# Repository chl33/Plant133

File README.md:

# Plant133

This is a full distribution of the Plant133 plant-watering device. This device can monitor and water up to 4 plants at a time. This repository hosts the firmware, PCBA design, and OpenSCAD code for all components.

A writeup about this project is at "[Plant1337: "Water 4 plants](https://selectiveappeal.org/posts/plant1337/)."

## Features

*   **Multi-Plant Support**: Monitors and independently waters up to 4 plants.
*   **Sensors**:
    *   Capacitive soil moisture sensing for each plant.
    *   SHTC3 temperature and humidity sensor for environmental monitoring.
    *   Reservoir water level float switch detection.
*   **User Interface**:
    *   **OLED Screen**: Rotates through status screens showing IP address, moisture levels, and environment data.
    *   **Web Dashboard**: A modern Svelte-based responsive web interface for real-time monitoring and configuration.
*   **Integration**:
    *   **MQTT**: Full support for Home Assistant auto-discovery and state reporting.
*   **Safety**:
    *   **Watchdog Timer**: Hardware watchdog protects against system hangs.
    *   **Dose Limiting**: Prevents over-watering by limiting the maximum number of pump cycles per day.
    *   **Reservoir Check**: Prevents pump damage by detecting low water levels.

## Usage

Please see the [instructions](instructions.md) for how to assemble and set up a Plant133 device hardware.

## Development

### Prerequisites
*   [PlatformIO](https://platformio.org/) (Core or VSCode extension)
*   [Node.js](https://nodejs.org/) (for building the web interface)

### Building and Flashing Firmware

1.  **Configure Secrets**: Copy `secrets.ini.example` to `secrets.ini` and set your WiFi credentials, OTA password, and MQTT details.
2.  **Onetime setup for building the web interface**:
    ```bash
	cd svelte
	npm install
	```
3.  **Build the Web interface and Firmware**:
    ```bash
    # For a specific board (e.g. usb_cactus)
    pio run -e usb_cactus
    ```
4.  **Upload Firmware**:
    ```bash
    pio run -e usb_cactus -t upload
    ```

## API Reference

The device exposes a JSON API for integration and control:

*   `GET /api/status`: Returns system status (temp, humidity, water level, MQTT connection).
*   `GET /api/plants`: Returns configuration for all plants.
*   `GET /api/moisture`: Returns current moisture readings and watering states.
*   `PUT /api/plants/{id}`: Update configuration for a specific plant.
*   `GET /api/wifi`: Get current WiFi SSID and board name.
*   `GET /api/mqtt`: Get MQTT configuration status.
*   `POST /test/pump`: Run a pump for a specific duration (JSON body: `{ "pumpId": 1, "duration": 1000 }`).
*   `POST /api/restart`: Restart the device.

## Software Libraries

This project is built using a custom C++ framework for ESP devices:
- [og3](https://github.com/chl33/og3): Application framework.
- [og3x-oled](https://github.com/chl33/og3x-oled): OLED screen support.
- [og3x-shtc3](https://github.com/chl33/og3x-shtc3): SHTC3 sensor support.
- [svelteesp32](https://github.com/BCsabaEngine/svelteesp32): Web interface integration.

## Hardware

### PCBA

The full [KiCAD](https://www.kicad.org/) project for the printed circuit board is in the [KiCAD](KiCAD/) subdirectory.

### 3D Printed Components

Components are designed in [OpenSCAD](https://openscad.org/). Source code is in the [scad](scad/) subdirectory.

#### Project box
Housing for the PCBA ([scad/box/](scad/box/)).

#### Reservoir Hanger
Mounts the box to a water reservoir ([scad/ebox_hook](scad/ebox_hook)).

#### Reservoir Insert
Holds pumps and water level float ([scad/reservoir_insert](scad/reservoir_insert)).

#### Moisture Sensor Cap
Holds the watering tube at the sensor location ([scad/moisture_sensor_cap](scad/moisture_sensor_cap)).

#### Watering Spike
Alternative watering method using a soil spike ([scad/spike](scad/spike)).

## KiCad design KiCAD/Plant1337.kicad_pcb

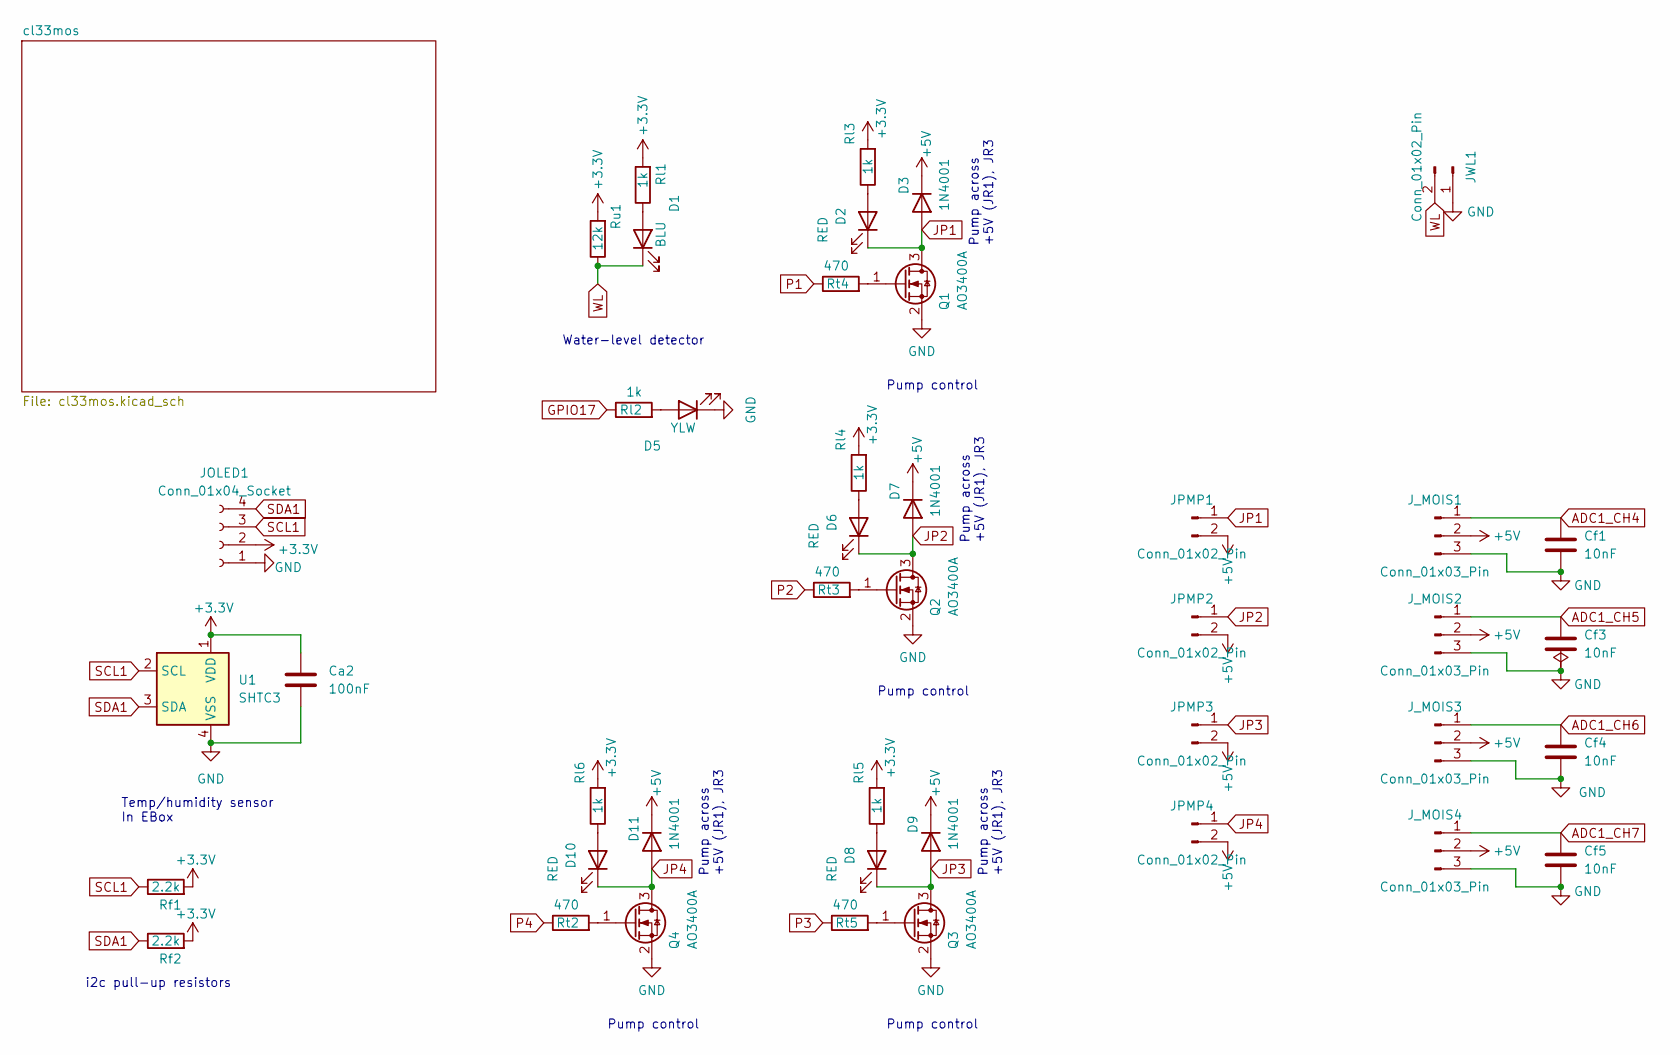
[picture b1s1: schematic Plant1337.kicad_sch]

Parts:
Ca2: 100nF; C_0603_1608Metric
Cf1, Cf3, Cf4, Cf5: 10nF; C_0603_1608Metric_Pad1.08x0.95mm_HandSolder
D1: BLU; LED_0603_1608Metric
D2, D6, D8, D10: RED; LED_0603_1608Metric
D3, D7, D9, D11: 1N4001; D_SMA
D5: YLW; LED_0603_1608Metric
JOLED1: Conn_01x04_Socket; PinSocket_1x04_P2.54mm_Vertical
JPMP1, JPMP2, JPMP3, JPMP4: Conn_01x02_Pin; JST_XH_B2B-XH-A_1x02_P2.50mm_Vertical
JWL1: Conn_01x02_Pin; JST_XH_B2B-XH-A_1x02_P2.50mm_Vertical
J_MOIS1, J_MOIS2, J_MOIS3, J_MOIS4: Conn_01x03_Pin; JST_XH_B3B-XH-A_1x03_P2.50mm_Vertical
Q1, Q2, Q3, Q4: AO3400A; SOT-23
Rf1, Rf2: 2.2k; R_0603_1608Metric
Rl1, Rl2, Rl3, Rl4, Rl5, Rl6: 1k; R_0603_1608Metric
Rt2, Rt3, Rt4, Rt5: 470; R_0603_1608Metric
Ru1: 12k; R_0603_1608Metric
U1: SHTC3; Sensirion_DFN-4-1EP_2x2mm_P1mm_EP0.7x1.6mm

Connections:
+3.3V: Ca2.1, JOLED1.2, Rf1.2, Rf2.2, Rl1.2, Rl3.2, Rl4.2, Rl5.2, Rl6.2, Ru1.2, U1.1 (VDD); also elsewhere on the board
+5V: D3.1 (K), D7.1 (K), D9.1 (K), D11.1 (K), JPMP1.2, JPMP2.2, JPMP3.2, JPMP4.2, J_MOIS1.2, J_MOIS2.2, J_MOIS3.2, J_MOIS4.2; also elsewhere on the board
ADC1_CH4: Cf1.2, J_MOIS1.1; also elsewhere on the board
ADC1_CH5: Cf3.2, J_MOIS2.1; also elsewhere on the board
ADC1_CH6: Cf4.2, J_MOIS3.1; also elsewhere on the board
ADC1_CH7: Cf5.2, J_MOIS4.1; also elsewhere on the board
GND: Ca2.2, Cf1.1, Cf3.1, Cf4.1, Cf5.1, D5.1 (K), JOLED1.1, JWL1.1, J_MOIS1.3, J_MOIS2.3, J_MOIS3.3, J_MOIS4.3, Q1.2 (S), Q2.2 (S), Q3.2 (S), Q4.2 (S), U1.4 (VSS); also elsewhere on the board
GPIO17: Rl2.1; also elsewhere on the board
JP1: D2.1 (K), D3.2 (A), JPMP1.1, Q1.3 (D)
JP2: D6.1 (K), D7.2 (A), JPMP2.1, Q2.3 (D)
JP3: D8.1 (K), D9.2 (A), JPMP3.1, Q3.3 (D)
JP4: D10.1 (K), D11.2 (A), JPMP4.1, Q4.3 (D)
unnamed: D1.2 (A), Rl1.1
unnamed: D2.2 (A), Rl3.1
unnamed: D5.2 (A), Rl2.2
unnamed: D6.2 (A), Rl4.1
unnamed: D8.2 (A), Rl5.1
unnamed: D10.2 (A), Rl6.1
unnamed: Q1.1 (G), Rt4.2
unnamed: Q2.1 (G), Rt3.2
unnamed: Q3.1 (G), Rt5.2
unnamed: Q4.1 (G), Rt2.2
P1: Rt4.1; also elsewhere on the board
P2: Rt3.1; also elsewhere on the board
P3: Rt5.1; also elsewhere on the board
P4: Rt2.1; also elsewhere on the board
SCL1: JOLED1.3, Rf1.1, U1.2 (SCL); also elsewhere on the board
SDA1: JOLED1.4, Rf2.1, U1.3 (SDA); also elsewhere on the board
WL: D1.1 (K), JWL1.2, Ru1.1; also elsewhere on the board

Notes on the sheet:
i2c pull-up resistors
Pump control
Pump across +5V (JR1), JR3
Water-level detector
Temp/humidity sensor In EBox

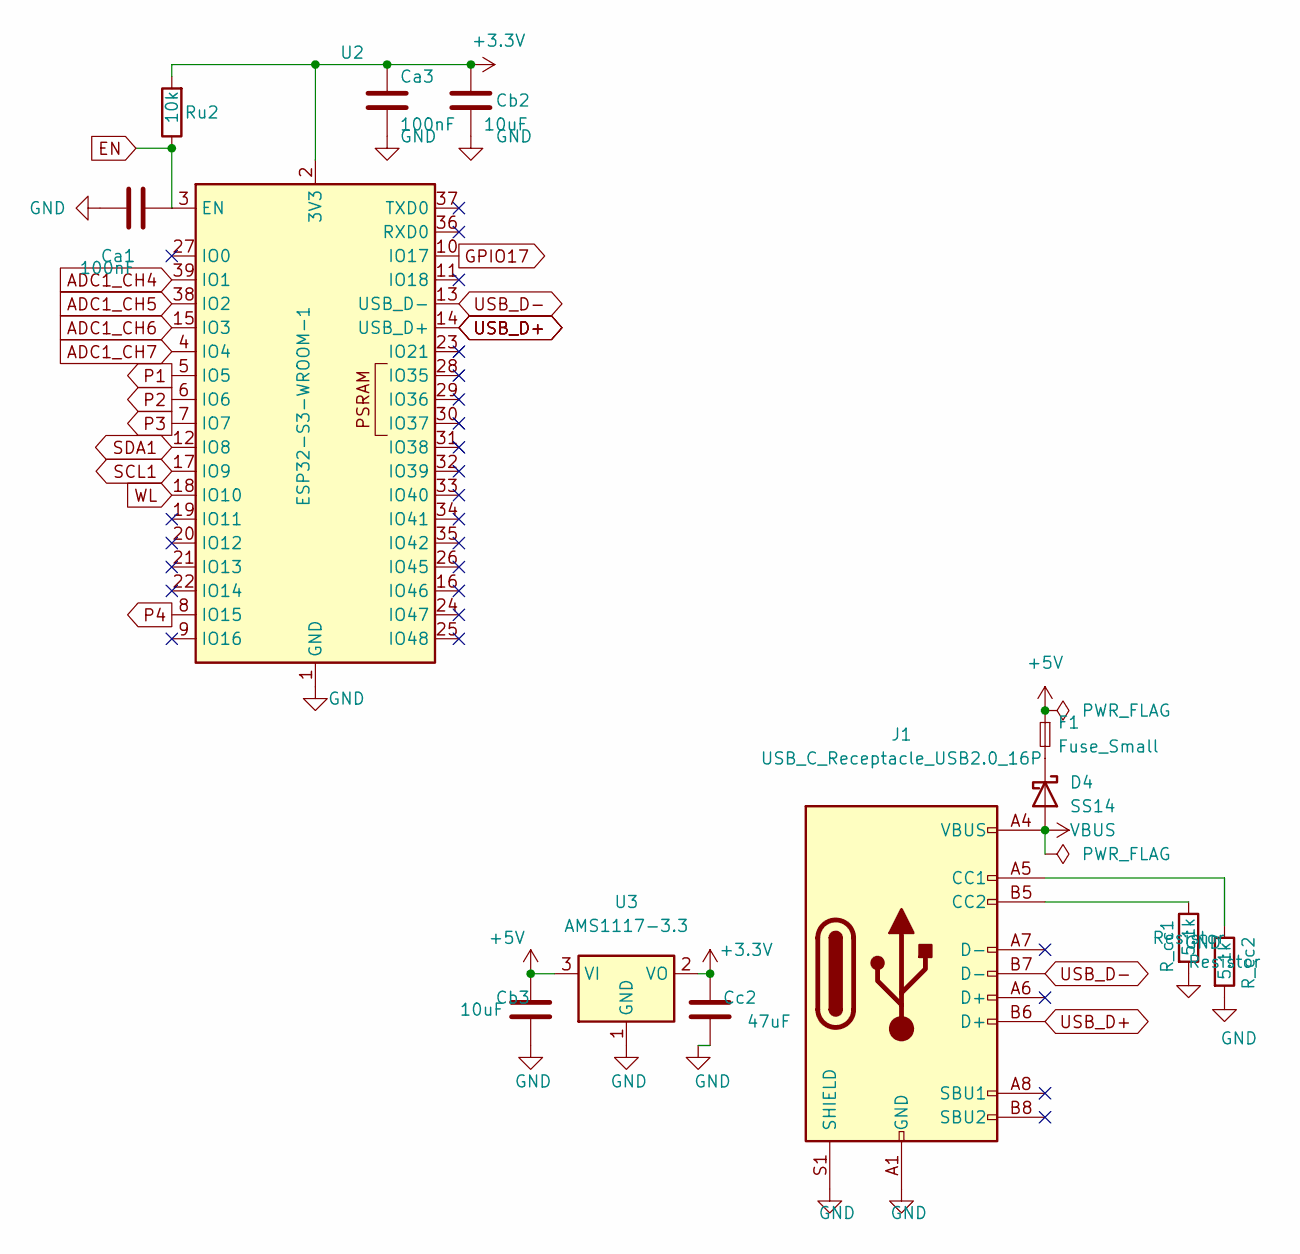
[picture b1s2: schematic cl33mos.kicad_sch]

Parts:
Ca1, Ca3: 100nF; C_0603_1608Metric
Cb2, Cb3: 10uF; C_0805_2012Metric_Pad1.18x1.45mm_HandSolder
Cc2: 47uF; C_0805_2012Metric_Pad1.18x1.45mm_HandSolder
D4: SS14; D_SMA
F1: Fuse_Small; D_0805_2012Metric
J1: USB_C_Receptacle_USB2.0_16P; USB_C_Receptacle_HRO_TYPE-C-31-M-12
R_cc1, R_cc2: 5.1k; R_0603_1608Metric
Ru2: 10k; R_0603_1608Metric
U2: ESP32-S3-WROOM-1
U3: AMS1117-3.3; SOT-223-3_TabPin2

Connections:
+3.3V: Ca3.1, Cb2.1, Cc2.1, Ru2.2, U2.2 (3V3), U3.2 (VO); also elsewhere on the board
+5V: Cb3.1, F1.1, U3.3 (VI); also elsewhere on the board
ADC1_CH4: U2.39 (IO1); also elsewhere on the board
ADC1_CH5: U2.38 (IO2); also elsewhere on the board
ADC1_CH6: U2.15 (IO3); also elsewhere on the board
ADC1_CH7: U2.4 (IO4); also elsewhere on the board
EN: Ca1.2, Ru2.1, U2.3 (EN)
GND: Ca1.1, Ca3.2, Cb2.2, Cb3.2, Cc2.2, J1.A1 (GND), J1.A12 (GND), J1.B1 (GND), J1.B12 (GND), J1.S1 (SHIELD), R_cc1.2, R_cc2.2, U2.1 (GND), U2.40 (GND), U2.41 (GND), U3.1 (GND); also elsewhere on the board
GPIO17: U2.10 (IO17); also elsewhere on the board
unnamed: D4.1 (K), F1.2
unnamed: J1.A5 (CC1), R_cc2.1
unnamed: J1.B5 (CC2), R_cc1.1
P1: U2.5 (IO5); also elsewhere on the board
P2: U2.6 (IO6); also elsewhere on the board
P3: U2.7 (IO7); also elsewhere on the board
P4: U2.8 (IO15); also elsewhere on the board
SCL1: U2.17 (IO9); also elsewhere on the board
SDA1: U2.12 (IO8); also elsewhere on the board
USB_D+: J1.B6 (D+), U2.14 (USB_D+)
USB_D-: J1.B7 (D-), U2.13 (USB_D-)
VBUS: D4.2 (A), J1.A4 (VBUS), J1.A9 (VBUS), J1.B4 (VBUS), J1.B9 (VBUS)
WL: U2.18 (IO10); also elsewhere on the board

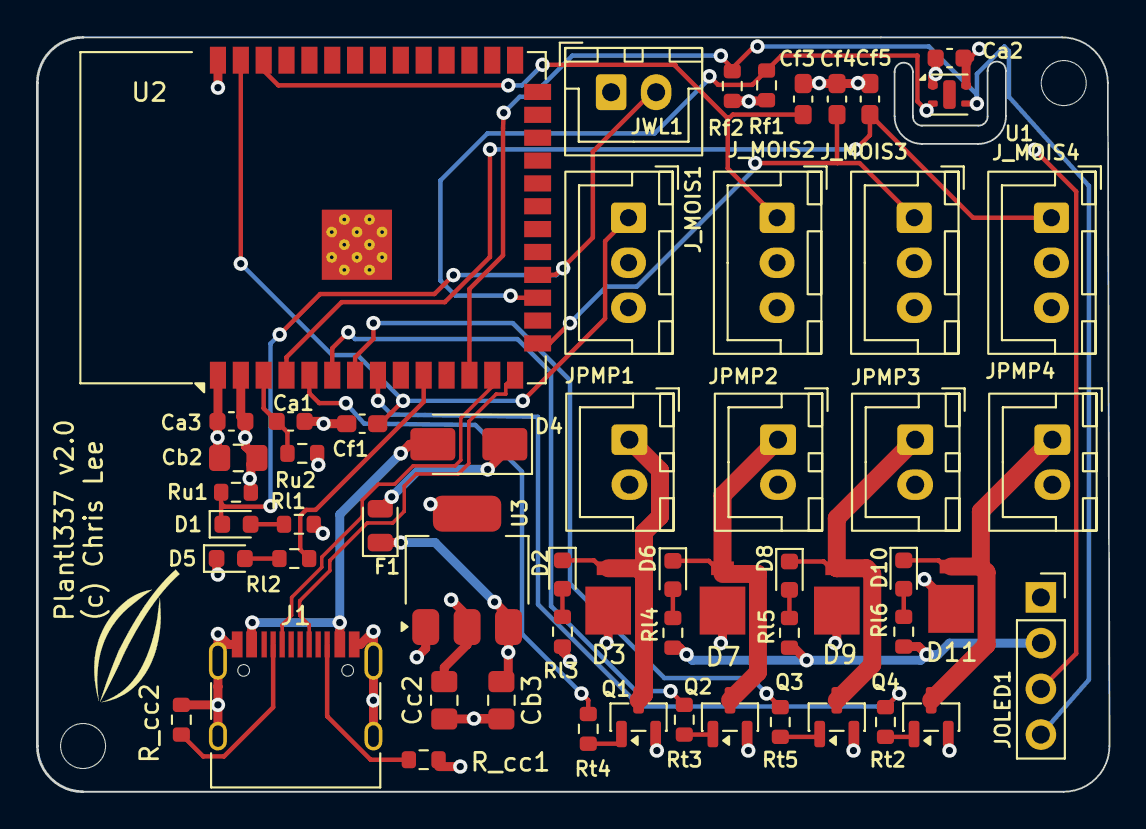
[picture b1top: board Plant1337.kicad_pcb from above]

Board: 4 copper layers, 59.6 x 41.9 mm, 56 parts (0 on the bottom side), 36 nets.

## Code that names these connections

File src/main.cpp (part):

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constexpr uint8_t kWaterPin = 23;
constexpr uint8_t kModeLED = 17;
// Soil moisture sensor ADC pin assignments for classic ESP32 (ADC1: GPIO 32, 33, 34, 35)
// - gpio32: adc1_ch4 -> mois1
// - gpio33: adc1_ch5 -> mois2
// - gpio34: adc1_ch6 -> mois3
// - gpio35: adc1_ch7 -> mois4
constexpr uint8_t kMoistureAnalogPin[4] = {32, 33, 34, 35};
// The pins on the v1.3 board. Changed pump-2 pin to not be on when power is first applied.
constexpr uint8_t kPumpCtlPin[4] = {18, 13, 16, 19};
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
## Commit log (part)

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2024-07-20 initial version
2024-07-20 Organize web pages by plant
2024-07-21 Add project box and utilities
2024-07-21 add readme
2024-07-21 add copyright check
2024-07-21 copyrights
2024-07-21 add pre-commit format check
2024-07-21 Initial content (#1)
    * initial version
    * Organize web pages by plant
    * Add project box and utilities
    * add readme
    * add copyright check
    * copyrights
2024-08-04 box: add screw-holes for box bottom, to attach to reservoir-hook
2024-08-04 fix watering state names
2024-08-04 Initial deployable software version
    - ADC/moisture pins for latest PCB version
    - OLED: graphical display of moisture states
    - Configuration page for reservoir pump-secs after float goes low
    - Offset timing of state machines for different plants
2024-08-04 added license
2024-08-04 copyright check: check .scad files
2024-08-04 Deployment 1 (#2)
    - box: add screw-holes for box bottom, to attach to reservoir-hook
    - fix watering state names
    - ADC/moisture pins for latest PCB version
    - OLED: graphical display of moisture states
    - Configuration page for reservoir pump-secs after float goes low
    - Offset timing of state machines for different plants
2024-08-04 add hump for OLED screen
2024-08-04 box: gui.py: button for launching OpenSCAD
2024-08-04 box update (#3)
    * add hump for OLED screen
    * box: gui.py: button for launching OpenSCAD
2024-08-09 update for og3 version0.2.0 (#4)
2024-08-10 finished porting to 0.2.0
2024-08-10 finished porting to 0.2.0 (#5)
2024-08-31 Move ebox to scad/box, and add number-labels for connectors.
2024-09-19 Update drawing of moisture level on OLED
    For each plant, scale so screen Y-range maps to twice min/max
    %-moisture targets and is centered between these.
2024-09-19 Add model of soil watering-spike.
2024-09-19 add platform-io compile check to workflow
2024-09-19 Openscad & code updates (#6)
    - Move EBox to a `scad/box` subdirectory, and add number-labels for plant connectors.
    - Improve drawing of moisture level on OLED screen
    - Add OpenSCAD model of a soil-spike with holes for watering.
    - Added compile-check
2024-09-19 LED blinking only for plant0
2024-09-21 improve comments in main.cpp
2024-09-21 KiCAD project for the Plant1337 PCB
2024-09-21 add reservoir insert OpenSCAD code
2024-09-21 fix Ebox
2024-09-21 OpenSCAD source for moisture sensor cap.
2024-09-21 update readme, add images
2024-09-21 readme fixes
2024-09-21 Comments, OpenSCAD sources, README updates (#8)
    * Improved comments in main.cpp
    * Added KiCAD project for the Plant1337 PCB
    * OpenSCAD models additions and fixes
    * reservoir insert
    * moisture sensor cap.
    * fixed Ebox
2024-09-21 fix photo link
2024-09-21 shrink spike photo
2024-09-21 add ebox_hook to README
2024-09-21 add ebox (#9)
2024-10-01 Update: watering library.json, ebox hook, reservoir insert
    - EBox hook: make top thicker for robustness
    - Rservoir insert: 4-pump version
2024-10-01 first draft of instructions
2024-10-02 update gitignore
2024-10-02 rename, update instructions
2024-10-02 link instructions in readme
2024-10-02 Add first draft of instructions (#11)
2024-10-06 README: point at new blog post
2024-10-06 new picture
2024-10-06 README: point at new blog post (#12)
    * README: point at new blog post
    * new picture
2024-10-16 add images to instructions
2024-10-16 more images
2024-10-16 add images to instructions (#13)
2024-10-16 fix spike img
2024-10-16 fix spike img (#14)
2024-10-17 add more images to instructions (#15)
2024-10-19 Make seconds between pump does configurable.
2024-10-19 CI workflow: rename example .ini before testing
2024-10-19 Make seconds between pump does configurable. (#16)
    Also:
    - version -> 0.7.2
    - move example .ini files into place before platformio test build in CI
2024-10-19 Limit number of pump doses in a watering cycle
    If there are too many pump doses in watering cycle, then switch to a
    "watering paused" state and wait for 12 hours.
    This is a safety features to avoid over-watering if something goes wrong,
    such as unreliable moisture sensor readings.
2024-10-19 Limit number of pump doses in a watering cycle (#17)
    If there are too many pump doses in watering cycle, then switch to a
    "watering paused" state and wait for 12 hours.
    This is a safety features to avoid over-watering if something goes wrong,
    such as unreliable moisture sensor readings.
2024-10-19 Document new watering configuration options.
2024-10-19 update watering config image
2024-10-19 Document new watering configuration options. (#18)
    * Document new watering configuration options.
    * update watering config image
2024-10-19 Update og3 library, logging tweaks
2024-10-19 Update og3 library, logging tweaks (#19)
2024-10-19 og3x-oled version -> 0.2.2
2024-10-19 og3x-oled version -> 0.2.2 (#20)
2024-10-20 Set AP password (#21)
    - If specified in secrets.ini, set a password on the soft-AP.
    - Also, switch mqtt client library to that used by ESPHome.
2024-10-20 update instructions for AP mode improvements
2024-10-20 update instructions for AP mode improvements (#22)
2024-10-20 update deps: og3x-oled
2024-10-20 update deps: og3x-oled (#23)
2024-10-24 update workflows
2024-10-24 added license headers
2024-10-24 tweak workflow
2024-10-24 update workflows (#24)
    * update workflows
    * added license headers
2024-11-03 Limit watering doses per day, across multiple watering cycles.
2024-11-04 comments
2024-11-07 Limit watering doses per day, across multiple watering cycles. (#25)
2024-12-31 Port to og3 0.2.5
2024-12-31 Ensure pump is off when not in a state which is explicitly watering.
2024-12-31 Ensure pump is off when not in a state which is explicitly watering. (#27)
2025-01-11 Update KiCAD model
2025-01-12 Update KiCAD model (#28)
2025-01-20 Fix limiting doses in 24 hours.
    Use 64-bit clock values to avoid problems with value rollover.
2025-01-20 software version -> 0.8.0
2025-01-21 Simplify dose tracking, add some logging.
2025-01-23 Make end of watering-pause to be more consistent.
2025-01-23 dose tracking: minor tweak, update/fix comments
2025-01-24 Fix limiting doses in 24 hours. (#29)
    - Fix limiting doses in 24 hours.
    - Use 64-bit clock values to avoid problems with value rollover.
    - Make end of watering-pause to be more consistent.
    - software version -> 0.8.0
2025-06-28 Upgrade version of og3
    The new version of og3 does not support appending the variable-group name to variable
    names. In this version, we simply construct variable ids this way manually.
2025-07-22 Make a separate HA-discovery device for each plant
2025-07-30 DoseLog variables need per-plant differentiation
2025-08-01 HA discovery: set parent device for plants-devices
2025-08-01 version -> 0.8.3
2025-08-01 update copyright checker
2025-08-01 fix path
2025-08-01 fix license check again
2025-08-01 again
2025-08-01 ci fix?
2025-08-01 Version 0.8.3 (#30)
    * Make a separate HA-discovery device for each plant
    * Updated year in copyright notices
    * HA discovery: set parent device for plants-devices
    * version -> 0.8.3
    * update copyright checker
2025-08-10 KiCAD update -> v1.3. Change pump2 DIO, remove pump pull-downs
2025-10-05 board v1.3, test web page
2025-10-11 svelte app interface in progress
2025-10-12 Import svelte interface, add wifi API web backends
2025-10-12 MQTT svelte-config support added
2025-10-12 Layouty improvement from claude
2025-10-12 Add more config and status for each plant
2025-10-12 Failed (so far) attempt to display board top bar
2025-10-12 Claude: optimize for narrower (cellphone) screens
2025-10-13 Improvements
    - Fix setting plant "enabled" from svelte-interface
    - Fix saving mqtt/wifi config when updated from svelte-interface
    - Display improvements to interface
    - Include color bands for moisture gauge
    - Show raw moisture readings in config interface, for setting calibration values
2025-10-14 Compress gauge display on svelte overview page
2025-10-14 watering state machine: setState() updates m_watering_enabled.
2025-10-14 svelte interface: config via gear icon, update dose and status
2025-10-14 update version
2025-10-14 svelte interface: remove 0-100% at bottom of gauge
2025-10-15 svelte interface: MQTT connection indicator, sw/hw versions
2025-10-15 attempt to get CI to build svelte app
2025-10-18 attempt to fix CI build
2025-10-18 README: mention svelte web interface
2025-10-18 attempt to fix the CI build
2025-10-18 another attempt to fix the CI build
2025-10-18 update example secret.init files
2025-10-19 dependency update
2025-10-19 Use lib_compat_mode = strict to try to get code to compile
    Suggesed in https://community.platformio.org/t/im-having-trouble-with-library-dependencies-for-my-project/52855/2
2025-10-19 Add svelte-based web interface (#31)
    - Add svelte-based web UI developed with the help of claude.
    - KiCAD update -> v1.3. Change pump2 DIO, remove pump pull-downs
    - board v1.3, test web page
    The old interface can still be reached by at the "/root" path.
2025-10-19 Update README with svelte-interface picture
2025-10-19 README: mention the use of svelteesp32.
2025-10-23 KiCad updates, OpenSCAD design for PCB-stencil holder
2025-11-02 Added-back screw-holes at 2 corners of the board
2025-11-02 og3 -> 0.3.96
2025-11-28 gemini added: pump test button, app restart button
2025-11-28 Update software version, delete TODOs
2025-11-28 Multiple improvements (#33)
    - Version -> 0.9.2
    - Updated version of KiCAD
    - OpenSCAD design for PCB/stencil holder
    - Added screw holes in corners of PCB
    - Updated Web interface (gemini)
    - Restart button
2025-11-28 Use a watchdog timer for safety when pumping water (gemini)
2025-11-28 Use a watchdog timer for safety when pumping water (gemini) (#34)
2025-11-29 Disable watchdog timer during OTA firmware update
2025-11-29 Disable watchdog timer during OTA firmware update (#35)
2025-11-29 version bump: og3 version update
2025-11-29 Bump og3 again, revised README (gemini)
2025-11-29 tweaked readme
2025-11-29 Updated instructions (gemini)
2025-11-29 Updated instructions
2025-11-29 add missing images
2025-11-29 final instructions tweaks
2025-11-29 version bump: og3 version update (#36)
    * version bump: og3 version update
    * Revised README (gemini)
    * Updated instructions (gemini)
    * Updated instructions with newer interface images
2025-11-29 Have "pio run" build the svelte interface.
2025-11-29 Update build script
2025-12-13 Use og3 0.4.0, packages Watchdog
2025-12-14 version 0.9.5 (#37)
    * Have "pio run" build the svelte interface.
    * Use og3 0.4.0, packages Watchdog
2026-01-28 Update readme for setup for the build
2026-01-28 fix description
2026-01-28 Update readme for setup for the build (#38)
2026-02-01 Version 0.9.6: allow disabling MQTT
    This allows not publishing values while calibrating the moisture sensor.
2026-02-01 Version 0.9.6: allow disabling MQTT (#39)
    This allows not publishing values while calibrating the moisture sensor.
2026-03-01 license header util update
2026-03-01 license header update
2026-03-06 updates for newer PsychicHttp
2026-03-06 Remove sed fixes from older PsychicHttp version
2026-03-06 Re-organizing platform.ini
2026-03-06 CI: separate svelte build step is now redundant
2026-03-07 Web interface updates
    Indicate whether:
    - Device is online/offline
    - Watering of each plant is enabled
    - Connected to MQTT broker
2026-03-07 Only update filtered moisture sensor value if raw val is reasonable.
2026-03-08 gemini updates for the CI build
2026-03-08 setup local.ini when running CI
2026-03-08 ci test with usb_spider
2026-03-08 README updates by gemini
2026-03-08 Use og3 for update web server, mqtt client (WIP) (#40)
    * license header util update
    * license header update
    * Gemini ported to og3 0.5.0 pre-release
    * updates for newer PsychicHttp
    * Re-organized platform.ini
    * CI: separate svelte build step is now redundant
2026-04-19 fix build

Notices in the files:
src/main.cpp:
Copyright (c) 2026 Chris Lee and contributors.
Licensed under the MIT license. See LICENSE file in the project root for details.
